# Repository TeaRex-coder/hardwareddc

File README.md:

<h1 align="center">HardwareDDC</h1>
<h4 align="center">A custom PCB that makes adjusting monitor settings easy and convenient</h4>

<!-- Horizontal layout with 3 images -->

## What is DDC?

DDC/CI (Display Data Channel Command Interface) lets you control monitors with software instead of navigating the nipple or rear buttons. In a perfect world, we could control all monitors with DDC, but unfortunately, that's not the case...

- Some monitors simply don't support DDC :(
- Some monitors like Samsung's G9 ultrawides support DDC only on HDMI
- \*nix (i.e. macOS & Linux) users of DisplayLink don't have DDC support
- Your monitor only supports DDC through HDMI (not DisplayPort)

If you're in one of those last three situations HardwareDDC might be for you! It uses an ESP32 to send raw I<sup>2</sup>C DDC signals to your monitor's HDMI port while another port is used for video.

## Getting Started

HardwareDDC features an ESP32 with reset and boot buttons, an HDMI connector exposing GND, SDA and SCL, and it's powered by USB-C which also exposes the UART console. Optionally, it can be powered by 5V directly through the GPIO pins, and additional GPIO pins are available for debugging and future expandability.

The PCB and the 3D printed ABS case are available on the [website](https://hardwareddc.alexandreboutoille.com), and the files can be found [here](./hardware/README.md).

Once you have your board, you can flash the firmware with the [web installer](https://hardwareddc.alexandreboutoille.com).

Controlling HardwareDDC is done through hotkeys, instructions can be found [here](./ui/README.md)

---

## Sponsors

Thank you PCBWay for sponsoring this project providing PCB prototyping <3

<details>
<summary>Review & Opinions</summary>

TL;DR Would I recommend PCBWay's PCB service? Yes!

It's impossible for me to provide an unbiased opinion as PCBWay has provided boards free of charge to help me work on this project. However, my experience was overall positive. Starting with their marketing rep Liam, he offered a partnership respectfully and fairly. When placing the order, the team helped me, a novice to PCB design and PCBWay's services, follow some best practices regarding board design and ordering. Finally, the production tracker helped keep my curious mind informed and the assembled product functioned as intended.

When researching PCBWay's brand before agreeing to a partnership, I noticed a customer expressing disappointment in the assembly of an HDMI connector. I took this with a grain of salt, as the dissatisfied customers are generally the loudest, but it was still a concern. The boards I received had well-soldered DisplayPort connector pins to a level as good, if not better than I could do by hand.

I hope the experience I received is representative of any regular PCBWay customer despite PCBWay expecting a review. If you need PCB prototyping for your project, consider giving them a go :)

</details>

Thank you Flux AI for providing [breakout boards](./experiments/hardwareddc-aux-breakout) for HardwareDDC <3

## Future Ideas

- [x] Improve Microsoft Windows UX/Create Proper User Interface
  - [ ] Add more information to GUI (e.g. connection status)
  - [ ] Enable user-modifiable hotkeys
- [ ] Support Multiple Monitors
- [ ] Create a non-network-based approach

## Extras

Shoutout to these projects that make HardwareDDC possible:

- [ESP Web Tools](https://github.com/esphome/esp-web-tools)
- [Improv Wi-Fi](https://github.com/jnthas/Improv-WiFi-Library)
- [DDC/CI VCP library](https://github.com/tttttx2/ddcvcp)

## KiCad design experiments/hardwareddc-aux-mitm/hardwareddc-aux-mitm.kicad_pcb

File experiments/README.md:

# HardwareDDC Experiments

_I do a lot of work behind the scene to learn about DDC-related tech. In this directory, I want to share some of my fun HardwareDDC experiments._

## HardwareDDC Aux V1.0

This board uses the [PTN3392](https://www.nxp.com/docs/en/data-sheet/PTN3392.pdf) DisplayPort to VGA IC to convert DP Aux into i2c

Goals:

- Reduce latency
- No client software

[Schematic](./hardwareddc-aux-v1.0/hardwareddc-aux-v1.0.pdf)

[ECAD files](./hardwareddc-aux-v1.0/hardwareddc-aux-v1.0.zip)

Learnings:

- This solution is jank and pretty unstable
- Next time, I'll try using [TI's M-LVDS](https://www.ti.com/lit/ug/tidu599/tidu599.pdf) transceivers to interact with the Aux channel

## HardwareDDC Aux 2.0 "Breakout"

This board _attempts_ to "sniff" the DisplayPort auxiliary channel using [TI's SN65MLVD200AD](https://www.ti.com/lit/ds/symlink/sn65mlvd200a.pdf).

What I learned:

- How to better route high-speed differential pairs (DisplayPort video signal)
- Improved understanding of DisplayPort AUX

What didn't work:

- Sniffing the AUX channel

I think it didn't work because of my false assumptions of the physical hardware layout of DisplayPort AUX on both the source and sink. Possible also because of the assumptions I made before understanding the communication protocol.

In the future, I'll be trying using a more traditional Hardware layout as suggested in the DisplayPort 1.2 standards document to using a more MitM-like approach inspired by [JX5S' work](https://github.com/JX5S/DP_aux_emulator).

## HardwareDDC AUX 2.1 "MitM"

WIP

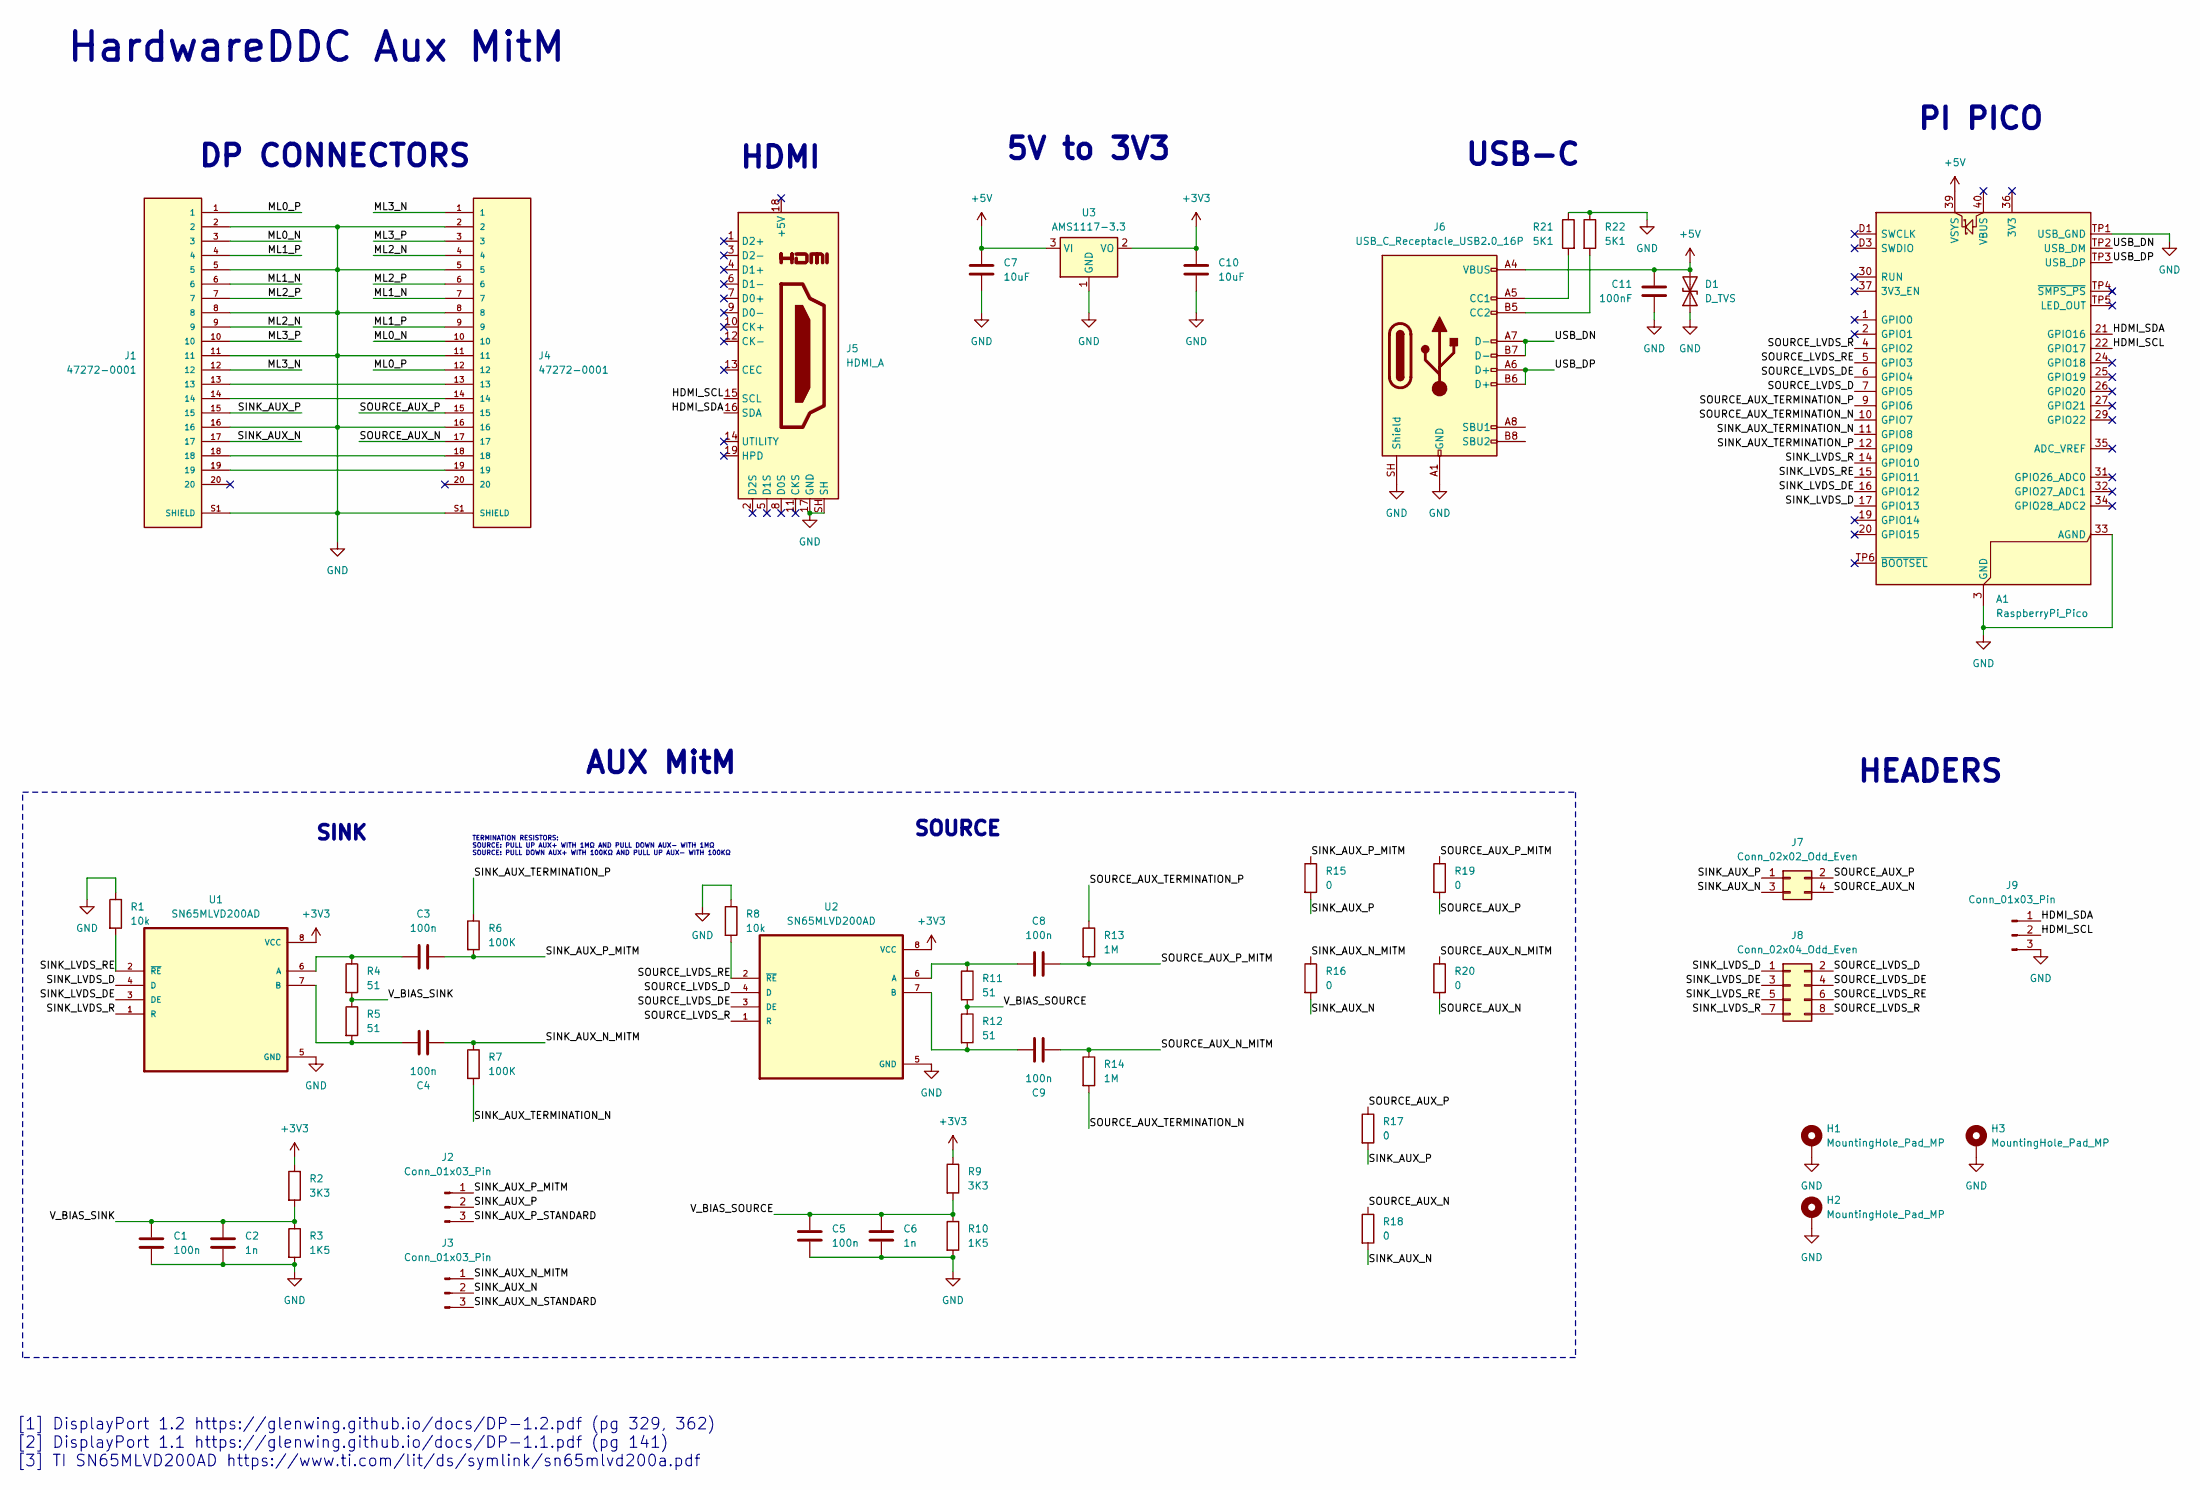
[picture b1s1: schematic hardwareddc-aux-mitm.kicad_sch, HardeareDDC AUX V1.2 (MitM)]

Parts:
A1: RaspberryPi_Pico; RaspberryPi_Pico_SMD
C1, C3, C4, C5, C8, C9: 100n; C_0402_1005Metric
C2, C6: 1n; C_0402_1005Metric
C7, C10: 10uF; C_0603_1608Metric
C11: 100nF; C_0603_1608Metric
D1: D_TVS; D_SOD-323
H1, H2, H3: MountingHole_Pad_MP; MountingHole_2.2mm_M2_ISO7380_Pad
J1, J4: 47272-0001; CONN_47272-0001_MOL
J2, J3: Conn_01x03_Pin
J5: HDMI_A; HDMI_A_Molex_208658-1001_Horizontal
J6: USB_C_Receptacle_USB2.0_16P; USB_C_Receptacle_GCT_USB4105-xx-A_16P_TopMnt_Horizontal
J7: Conn_02x02_Odd_Even; PinHeader_2x02_P2.54mm_Vertical
J8: Conn_02x04_Odd_Even; PinHeader_2x04_P2.54mm_Vertical
J9: Conn_01x03_Pin; PinHeader_1x03_P2.54mm_Vertical
R1, R8: 10k; R_0402_1005Metric
R2, R9: 3K3; R_0402_1005Metric
R3, R10: 1K5; R_0402_1005Metric
R4, R5, R11, R12: 51; R_0402_1005Metric
R6, R7: 100K; R_0402_1005Metric
R13, R14: 1M; R_0402_1005Metric
R15, R16, R17, R18, R19, R20: 0; R_0603_1608Metric
R21, R22: 5K1; R_0402_1005Metric
U1, U2: SN65MLVD200AD; SOIC-8_3.9x4.9mm_P1.27mm
U3: AMS1117-3.3; SOT-223-3_TabPin2

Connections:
+3V3: C10.1, R2.1, R9.1, U1.8 (VCC), U2.8 (VCC), U3.2 (VO)
+5V: A1.39 (VSYS), C7.1, C11.1, D1.2 (A2), J6.A4 (VBUS), J6.A9 (VBUS), J6.B4 (VBUS), J6.B9 (VBUS), U3.3 (VI)
/HDMI_SCL: A1.22 (GPIO17), J5.15 (SCL), J9.2
/HDMI_SDA: A1.21 (GPIO16), J5.16 (SDA), J9.1
/ML0_N: J1.3, J4.10
/ML0_P: J1.1, J4.12
/ML1_N: J1.6, J4.7
/ML1_P: J1.4, J4.9
/ML2_N: J1.9, J4.4
/ML2_P: J1.7, J4.6
/ML3_N: J1.12, J4.1
/ML3_P: J1.10, J4.3
/SINK_AUX_N: J1.17, J3.2, J7.3, R16.2, R18.2
/SINK_AUX_N_MITM: C4.2, J3.1, R7.1, R16.1
/SINK_AUX_P: J1.15, J2.2, J7.1, R15.2, R17.2
/SINK_AUX_P_MITM: C3.2, J2.1, R6.2, R15.1
/SINK_AUX_TERMINATION_N: A1.11 (GPIO8), R7.2
/SINK_AUX_TERMINATION_P: A1.12 (GPIO9), R6.1
/SINK_LVDS_D: A1.17 (GPIO13), J8.1, U1.4 (D)
/SINK_LVDS_DE: A1.16 (GPIO12), J8.3, U1.3 (DE)
/SINK_LVDS_R: A1.14 (GPIO10), J8.7, U1.1 (R)
/SINK_LVDS_RE: A1.15 (GPIO11), J8.5, R1.2, U1.2 (~RE)
/SOURCE_AUX_N: J4.17, J7.4, R18.1, R20.2
/SOURCE_AUX_N_MITM: C9.2, R14.1, R20.1
/SOURCE_AUX_P: J4.15, J7.2, R17.1, R19.2
/SOURCE_AUX_P_MITM: C8.2, R13.2, R19.1
/SOURCE_AUX_TERMINATION_N: A1.10 (GPIO7), R14.2
/SOURCE_AUX_TERMINATION_P: A1.9 (GPIO6), R13.1
/SOURCE_LVDS_D: A1.7 (GPIO5), J8.2, U2.4 (D)
/SOURCE_LVDS_DE: A1.6 (GPIO4), J8.4, U2.3 (DE)
/SOURCE_LVDS_R: A1.4 (GPIO2), J8.8, U2.1 (R)
/SOURCE_LVDS_RE: A1.5 (GPIO3), J8.6, R8.2, U2.2 (~RE)
/USB_DN: A1.TP2 (USB_DM), J6.A7 (D-), J6.B7 (D-)
/USB_DP: A1.TP3 (USB_DP), J6.A6 (D+), J6.B6 (D+)
/V_BIAS_SINK: C1.1, C2.1, R2.2, R3.1, R4.2, R5.1
/V_BIAS_SOURCE: C5.1, C6.1, R9.2, R10.1, R11.2, R12.1
GND: A1.3 (GND), A1.8 (GND), A1.13 (GND), A1.18 (GND), A1.23 (GND), A1.28 (GND), A1.33 (AGND), A1.38 (GND), A1.D2 (GND), A1.TP1 (USB_GND), C1.2, C2.2, C5.2, C6.2, C7.2, C10.2, C11.2, D1.1 (A1), H1.1 (MP_1), H2.1 (MP_1), H3.1 (MP_1), J1.2, J1.5, J1.8, J1.11, J1.16, J1.S1 (SHIELD), J1.S2 (SHIELD), J1.S3 (SHIELD), J1.S4 (SHIELD), J4.2, J4.5, J4.8, J4.11, J4.16, J4.S1 (SHIELD), J4.S2 (SHIELD), J4.S3 (SHIELD), J4.S4 (SHIELD), J5.17 (GND), J5.SH, J6.A1 (GND), J6.A12 (GND), J6.B1 (GND), J6.B12 (GND), J6.SH (Shield), J9.3, R1.1, R3.2, R8.1, R10.2, R21.1, R22.1, U1.5 (GND), U2.5 (GND), U3.1 (GND)
unnamed: J1.13, J4.13
unnamed: J1.14, J4.14
unnamed: J1.18, J4.18
unnamed: J1.19, J4.19
unnamed: J6.A5 (CC1), R21.2
unnamed: J6.B5 (CC2), R22.2
unnamed: C3.1, R4.1, U1.6 (A)
unnamed: C4.1, R5.2, U1.7 (B)
unnamed: C8.1, R11.1, U2.6 (A)
unnamed: C9.1, R12.2, U2.7 (B)

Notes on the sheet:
SOURCE
DP CONNECTORS
HardwareDDC Aux MitM
[1] DisplayPort 1.2 https://glenwing.github.io/docs/DP-1.2.pdf (pg 329, 362) [2] DisplayPort 1.1 https://glenwing.github.io/docs/DP-1.1.pdf (pg 141) [3] TI SN65MLVD200AD https://www.ti.com/lit/ds/symlink/sn65mlvd200a.pdf
HEADERS
AUX MitM
5V to 3V3
USB-C
PI PICO
SINK
TERMINATION RESISTORS: SOURCE: PULL UP AUX+ WITH 1MΩ AND PULL DOWN AUX- WITH 1MΩ SOURCE: PULL DOWN AUX+ WITH 100KΩ AND PULL UP AUX- WITH 100KΩ
HDMI

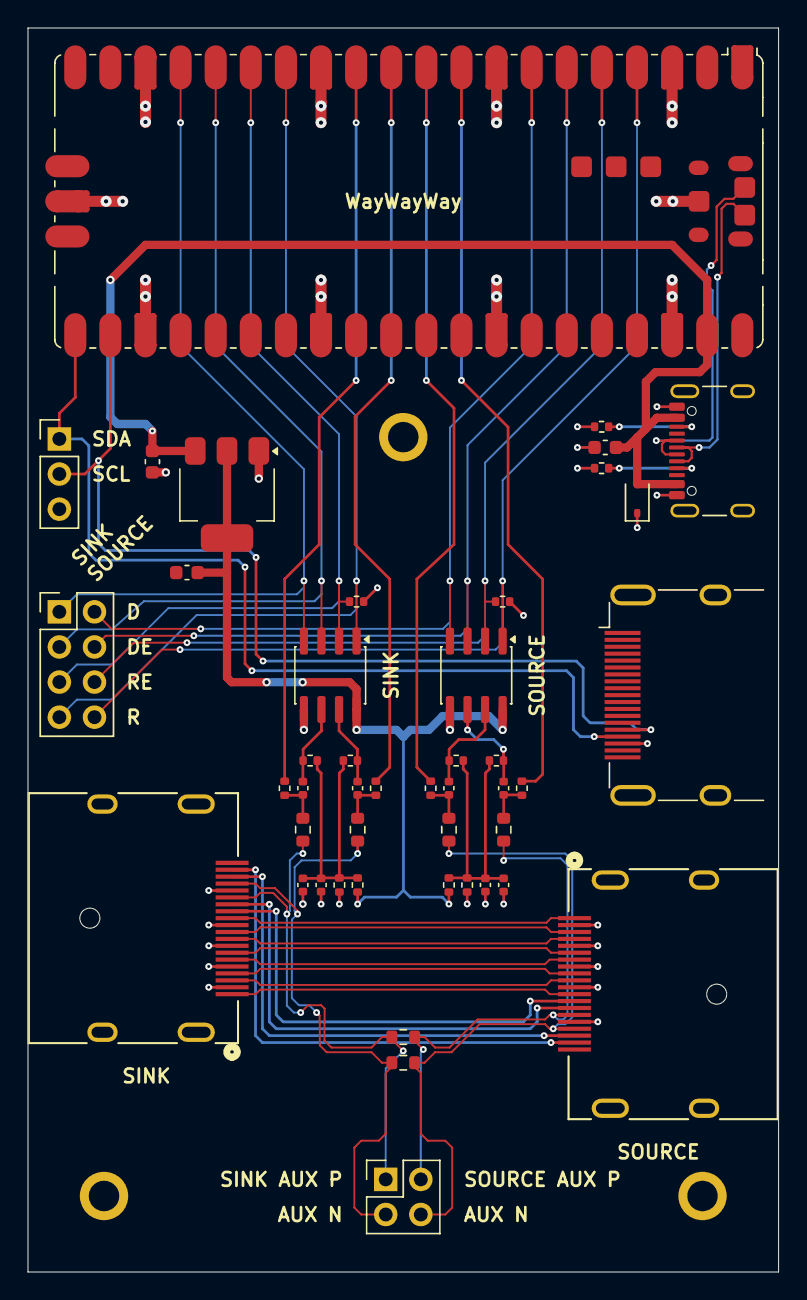
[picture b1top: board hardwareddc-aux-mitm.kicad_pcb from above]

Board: 4 copper layers, 54.3 x 90.0 mm, 48 parts (0 on the bottom side), 47 nets.

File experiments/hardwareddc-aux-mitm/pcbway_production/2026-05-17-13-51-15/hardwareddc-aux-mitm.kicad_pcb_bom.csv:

Designator,Quantity,Value,Footprint,Package,MPN,DNP,Mount_Type,Description,KiLib_Generator,MF,MP,Description_1,Price
"C1, C3, C4, C5, C8, C9",6,100n,C_0402_1005Metric,,,,smt,Unpolarized capacitor,SMD_2terminal_chip_molded,,,,
"C10, C7",2,10uF,C_0603_1608Metric,,,,smt,Unpolarized capacitor,SMD_2terminal_chip_molded,,,,
C11,1,100nF,C_0603_1608Metric,,,,smt,Unpolarized capacitor,SMD_2terminal_chip_molded,,,,
"C2, C6",2,1n,C_0402_1005Metric,,,,smt,Unpolarized capacitor,SMD_2terminal_chip_molded,,,,
D1,1,D_TVS,D_SOD-323,,,,smt,Bidirectional transient-voltage-suppression diode,,,,,
"J1, J4",2,47272-0001,CONN_47272-0001_MOL,,,,smt,,,Molex,472720001,,
J5,1,HDMI_A,HDMI_A_Molex_208658-1001_Horizontal,,,,smt,HDMI type A connector,,,,,
J6,1,USB_C_Receptacle_USB2.0_16P,USB_C_Receptacle_GCT_USB4105-xx-A_16P_TopMnt_Horizontal,,,,smt,USB 2.0-only 16P Type-C Receptacle connector,,,,,
J7,1,Conn_02x02_Odd_Even,PinHeader_2x02_P2.54mm_Vertical,,,,tht,"Generic connector, double row, 02x02, odd/even pin numbering scheme (row 1 odd numbers, row 2 even numbers), script generated (kicad-library-utils/schlib/autogen/connector/)",connector/pin_header_socket,,,,
J8,1,Conn_02x04_Odd_Even,PinHeader_2x04_P2.54mm_Vertical,,,,tht,"Generic connector, double row, 02x04, odd/even pin numbering scheme (row 1 odd numbers, row 2 even numbers), script generated (kicad-library-utils/schlib/autogen/connector/)",connector/pin_header_socket,,,,
"R1, R8",2,10k,R_0402_1005Metric,,,,smt,Resistor,SMD_2terminal_chip_molded,,,,
"R10, R3",2,1K5,R_0402_1005Metric,,,,smt,Resistor,SMD_2terminal_chip_molded,,,,
"R11, R12, R4, R5",4,51,R_0402_1005Metric,,,,smt,Resistor,SMD_2terminal_chip_molded,,,,
"R13, R14",2,1M,R_0402_1005Metric,,,,smt,Resistor,SMD_2terminal_chip_molded,,,,
"R15, R16, R17, R18, R19, R20",6,0,R_0603_1608Metric,,,,smt,Resistor,SMD_2terminal_chip_molded,,,,
"R2, R9",2,3K3,R_0402_1005Metric,,,,smt,Resistor,SMD_2terminal_chip_molded,,,,
"R21, R22",2,5K1,R_0402_1005Metric,,,,smt,Resistor,SMD_2terminal_chip_molded,,,,
"R6, R7",2,100K,R_0402_1005Metric,,,,smt,Resistor,SMD_2terminal_chip_molded,,,,
"U1, U2",2,SN65MLVD200AD,SOIC-8_3.9x4.9mm_P1.27mm,SOIC-8 Texas Instruments,,,smt,,package/gullwing,Texas Instruments,SN65MLVD200AD,Half-duplex M-LVDS transceiver,None
U3,1,AMS1117-3.3,SOT-223-3_TabPin2,,,,smt,"1A Low Dropout regulator, positive, 3.3V fixed output, SOT-223",,,,,

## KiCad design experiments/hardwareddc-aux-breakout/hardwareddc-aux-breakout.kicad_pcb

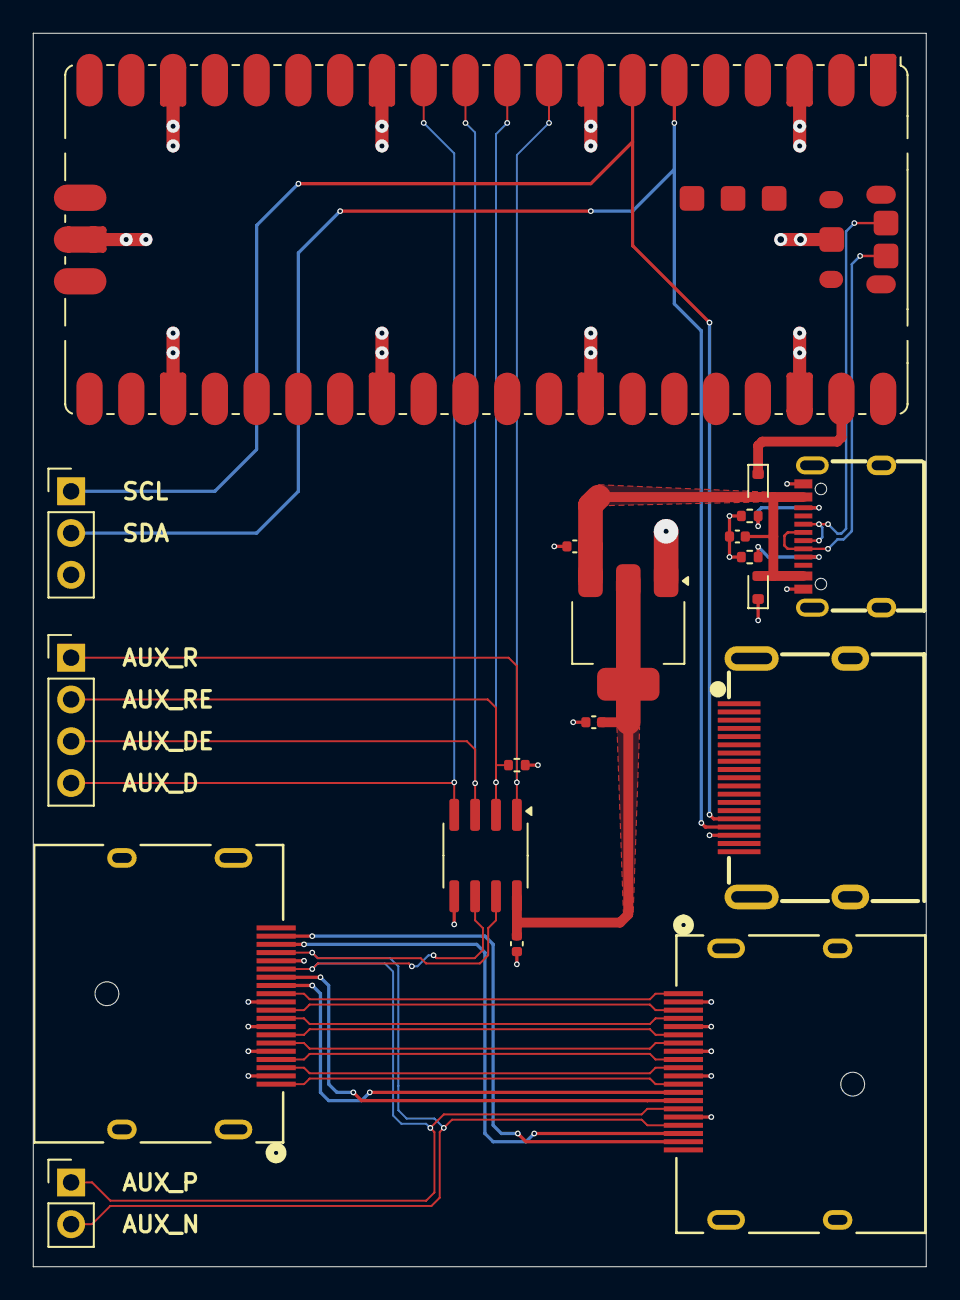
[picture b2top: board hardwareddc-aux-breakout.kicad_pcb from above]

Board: 4 copper layers, 54.3 x 75.0 mm, 19 parts (0 on the bottom side), 28 nets.

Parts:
A1: RaspberryPi_Pico; RaspberryPi_Pico_SMD
C1, C2: 100nF; C_0402_1005Metric
C3, C4: 10uF; C_0402_1005Metric
D1: D_TVS; D_SOD-523
D2: D_Schottky; D_SOD-523
J1: Conn_01x04_Pin; PinHeader_1x04_P2.54mm_Vertical
J2: USB_C_Receptacle; USB-C-SMD_TYPE-C-6PIN-2MD-073
J3: Conn_01x03_Pin; PinHeader_1x03_P2.54mm_Vertical
J4: Conn_01x02_Pin; PinHeader_1x02_P2.54mm_Vertical
J5, J6: 472720001; CONN_47272-0001_MOL
J7: HDMI_A_1.4; HDMI-SMD_HDMI-19PIN-043
R1, R2: 5.1K; R_0402_1005Metric
R3: 10K; R_0402_1005Metric
U1: SN65MLVD200ADR; SOIC-8_3.9x4.9mm_P1.27mm
U2: AMS1117-3.3; SOT-223-3_TabPin2

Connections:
+3V3: C2.1, C4.1, U1.8 (VCC), U2.2 (VO)
+5V: C1.1, C3.1, D1.2 (A2), D2.2 (A), J2.A4 (VBUS), U2.3 (VI)
/AUX_D: A1.12 (GPIO9), J1.4, U1.4 (D)
/AUX_DE: A1.11 (GPIO8), J1.3, U1.3 (DE)
/AUX_N: J4.2, J5.17, J6.17, U1.7 (B)
/AUX_P: J4.1, J5.15, J6.15, U1.6 (A)
/AUX_R: A1.9 (GPIO6), J1.1, U1.1 (R)
/AUX_RE: A1.10 (GPIO7), J1.2, R3.1, U1.2 (~RE)
/ML0_N: J5.3, J6.10
/ML0_P: J5.1, J6.12
/ML1_N: J5.6, J6.7
/ML1_P: J5.4, J6.9
/ML2_N: J5.9, J6.4
/ML2_P: J5.7, J6.6
/ML3_N: J5.12, J6.1
/ML3_P: J5.10, J6.3
/SCL: A1.7 (GPIO5), J3.1, J7.15 (SCL)
/SDA: A1.6 (GPIO4), J3.2, J7.16 (SDA)
/USB_DN: A1.TP2 (USB_DM), J2.A7 (D-), J2.B7 (D-)
/USB_DP: A1.TP3 (USB_DP), J2.A6 (D+), J2.B6 (D+)
GND: A1.3 (GND), A1.8 (GND), A1.13 (GND), A1.18 (GND), A1.23 (GND), A1.28 (GND), A1.33 (AGND), A1.38 (GND), A1.D2 (GND), A1.TP1 (USB_GND), C1.2, C2.2, C3.2, C4.2, D1.1 (A1), J2.A1 (GND), J2.S1 (SHIELD), J3.3, J5.2, J5.5, J5.8, J5.11, J5.16, J5.21, J5.22, J5.23, J5.24, J6.2, J6.5, J6.8, J6.11, J6.16, J6.21, J6.22, J6.23, J6.24, J7.17 (GND), J7.SH, R1.1, R2.1, R3.2, U1.5 (GND), U2.1 (GND)
unnamed: A1.39 (VSYS), D2.1 (K)
unnamed: J2.A5 (CC1), R1.2
unnamed: J2.B5 (CC2), R2.2
unnamed: J5.13, J6.13
unnamed: J5.14, J6.14
unnamed: J5.18, J6.18
unnamed: J5.19, J6.19

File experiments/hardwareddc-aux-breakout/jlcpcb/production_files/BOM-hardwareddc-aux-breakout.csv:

Comment,Designator,Footprint,LCSC,Quantity
100nF,"C1,C2",C_01005_0402Metric,C60474,2
10K,R3,R_0402_1005Metric,C60490,1
10uF,"C3,C4",C_0402_1005Metric,C105884,2
472720001,"J5,J6",CONN_47272-0001_MOL,C587824,2
5.1K,"R1,R2",R_01005_0402Metric,C105872,2
AMS1117-3.3,U2,SOT-223-3_TabPin2,C347222,1
Conn_01x02_Pin,J4,PinHeader_1x02_P2.54mm_Vertical,C492401,1
Conn_01x03_Pin,J3,PinHeader_1x03_P2.54mm_Vertical,C2937625,1
Conn_01x04_Pin,J1,PinHeader_1x04_P2.54mm_Vertical,C2691448,1
D_Schottky,D2,D_SOD-523,C727120,1
D_TVS,D1,D_SOD-523,C314264,1
HDMI_A_1.4,J7,HDMI-SMD_HDMI-19PIN-043,C2858275,1
RaspberryPi_Pico,A1,RaspberryPi_Pico_SMD,C42924268,1
SN65MLVD200ADR,U1,SOIC-8_3.9x4.9mm_P1.27mm,C695776,1
USB_C_Receptacle,J2,USB-C-SMD_TYPE-C-6PIN-2MD-073,C2765186,1

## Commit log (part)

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2024-06-27 toy v1
2024-06-27 toy v1.1
2024-06-27 toy v1.1.1
2024-06-27 toy v1.1.2
2024-06-28 toy v1.2
2024-07-11 toy v1.3
2024-07-11 toy v1.3.1
2024-07-12 toy v1.3.2
2024-07-17 update flasher
2024-07-17 update flasher ui
2024-07-17 update favicon
2024-07-17 installer styles
2024-07-17 changed web tools path
2024-07-17 cleanup
2024-07-22 mac ui
2024-07-22 remove test
2024-07-22 documentation
2024-07-24 update website
2024-07-25 update stripe
2024-07-25 update web README
2024-07-25 typo
2024-07-25 readme update
2024-07-25 Create LICENSE
2024-07-26 update shipping
2024-07-29 hardware docs
2024-08-03 update routes
2024-08-05 network update
2024-08-06 update ui
2024-08-06 replace binary
2024-08-06 update version
2025-01-12 update web
2025-01-29 update hardware
2025-01-29 update READMEs
2025-01-29 Bump golang.org/x/crypto from 0.23.0 to 0.31.0 in /ui/windows
    Bumps [golang.org/x/crypto](https://github.com/golang/crypto) from 0.23.0 to 0.31.0.
    - [Commits](https://github.com/golang/crypto/compare/v0.23.0...v0.31.0)
    ---
    updated-dependencies:
    - dependency-name: golang.org/x/crypto
    dependency-type: indirect
2025-02-14 installer workflow
2025-02-14 installer workflow fix
2025-04-05 PCBWay Sponsor
2025-04-05 HardwareDDC Aux V1.0
2025-04-05 PCBWay logo
2025-04-21 Update firmware: constrast support
2025-04-22 Update web: country clarification
2025-04-27 Update UI: janky mvp
2025-12-22 update web: stock update
2026-01-11 update: experiment documentation
2026-02-10 Update: README

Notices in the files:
experiments/hardwareddc-aux-mitm/hardwareddc-aux-mitm.kicad_pcb:
© 2026 Alexandre Boutoille
